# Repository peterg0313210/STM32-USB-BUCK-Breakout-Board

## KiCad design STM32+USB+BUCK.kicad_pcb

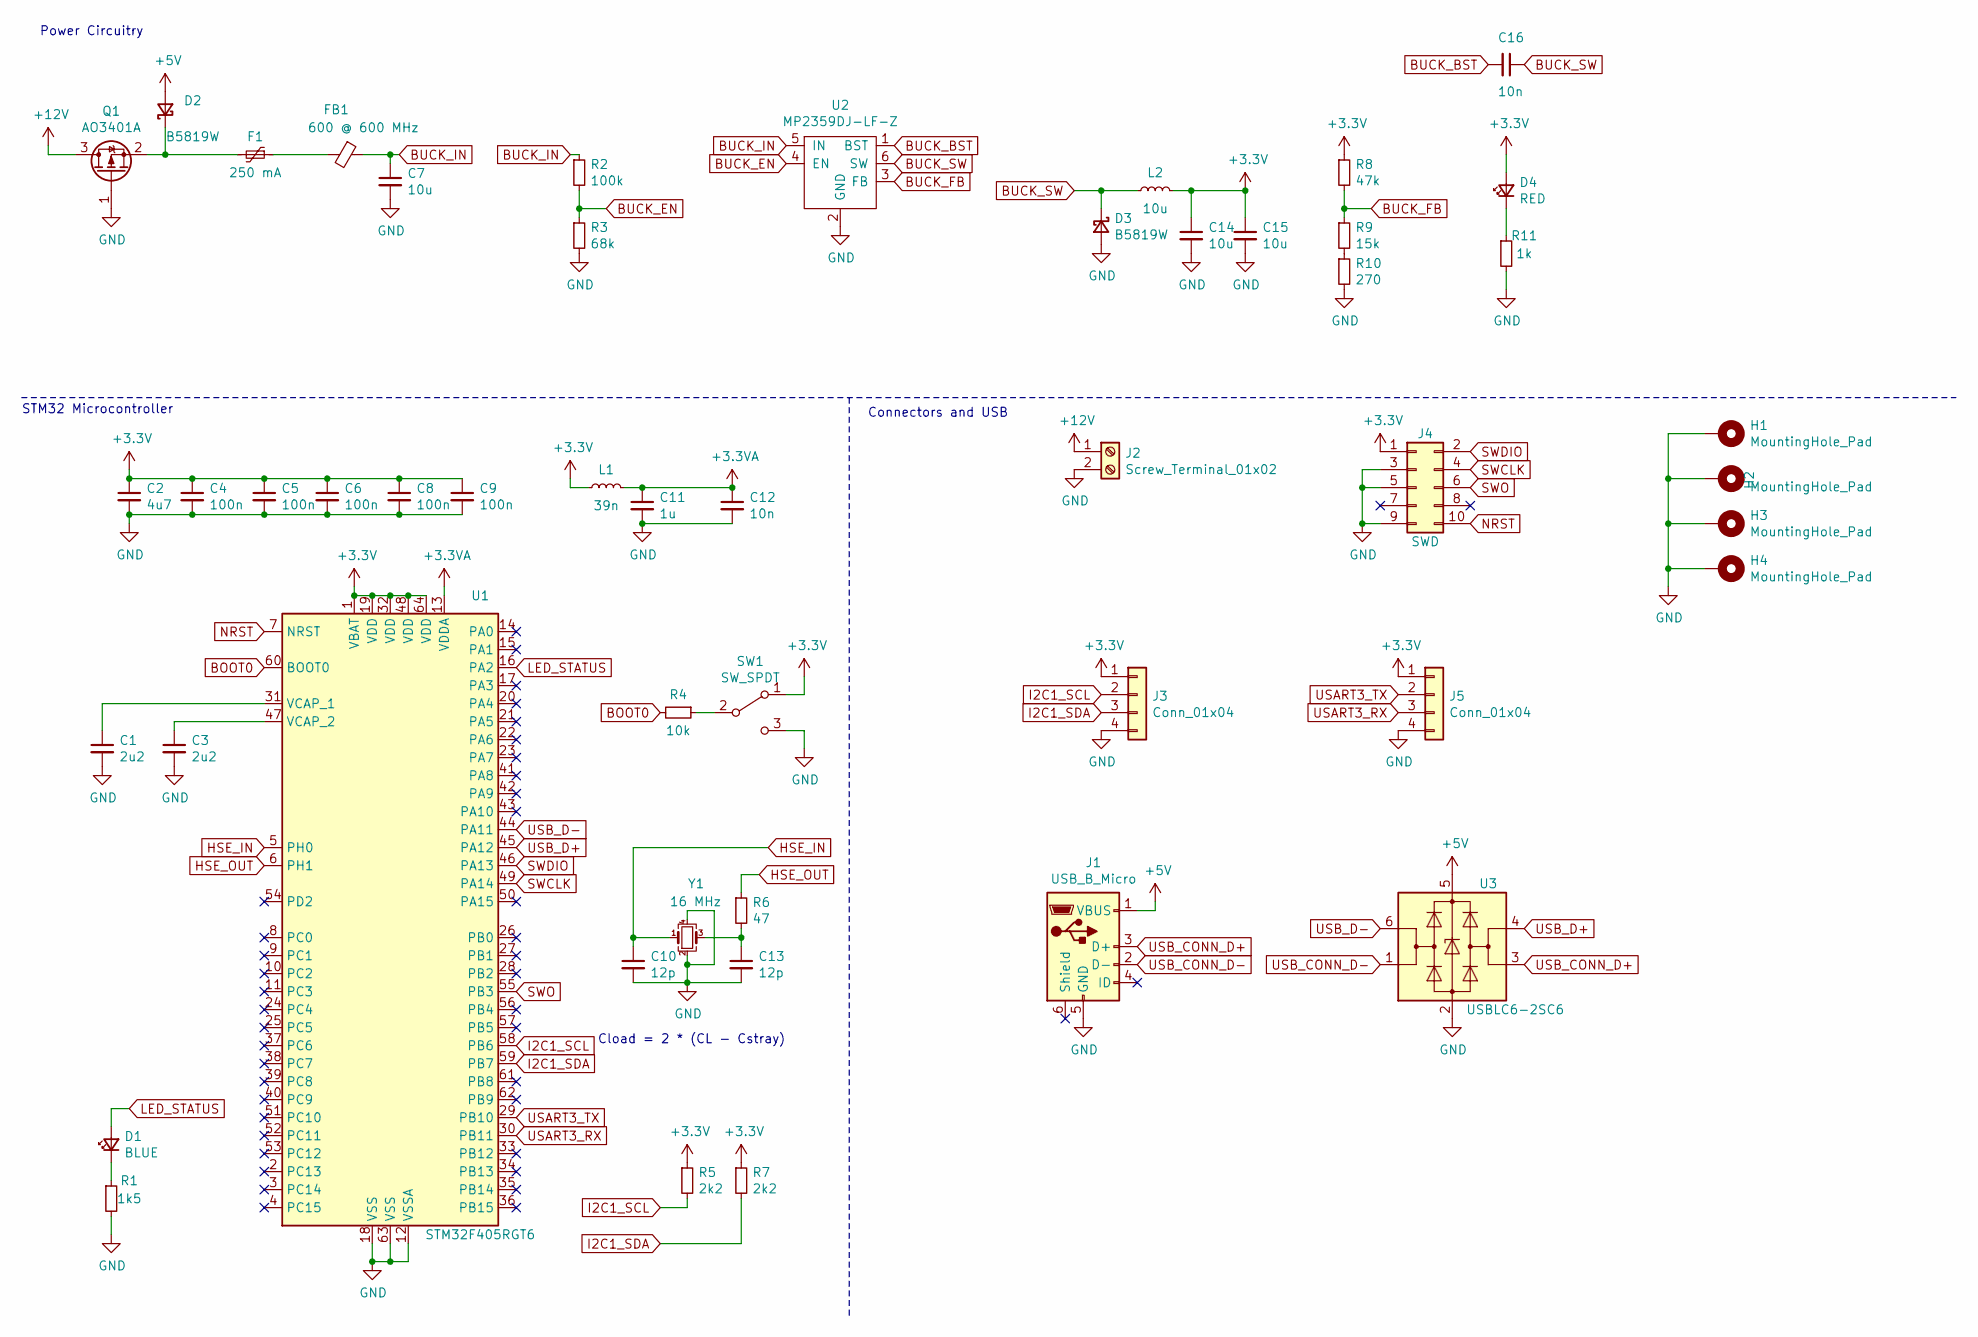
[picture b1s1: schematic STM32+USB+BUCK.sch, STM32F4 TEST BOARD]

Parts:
C1, C3: 2u2; C_0603_1608Metric
C2: 4u7; C_0603_1608Metric
C4, C5, C6, C8, C9: 100n; C_0402_1005Metric
C7, C14, C15: 10u; C_1206_3216Metric
C10, C13: 12p; C_0402_1005Metric
C11: 1u; C_0402_1005Metric
C12, C16: 10n; C_0603_1608Metric
D1: BLUE; LED_0603_1608Metric
D2, D3: B5819W; D_SOD-123
D4: RED; LED_0603_1608Metric
F1: 250 mA; Fuse_1206_3216Metric
FB1: 600 @ 600 MHz; L_0805_2012Metric
H1, H2, H3, H4: MountingHole_Pad; MountingHole_4.3mm_M4_Pad
J1: USB_B_Micro; USB_Micro-B_Molex-105017-0001
J2: Screw_Terminal_01x02; TerminalBlock_Phoenix_PT-1,5-2-3.5-H_1x02_P3.50mm_Horizontal
J3, J5: Conn_01x04; Molex_PicoBlade_53048-0410_1x04_P1.25mm_Horizontal
J4: SWD; PinHeader_2x05_P1.27mm_Vertical_SMD
L1: 39n; L_0402_1005Metric
L2: 10u; L_Sunlord_MWSA0518_5.4x5.2mm
Q1: AO3401A; SOT-23
R1: 1k5; R_0603_1608Metric
R2: 100k; R_0603_1608Metric
R3: 68k; R_0603_1608Metric
R4: 10k; R_0402_1005Metric
R5, R7: 2k2; R_0402_1005Metric
R6: 47; R_0402_1005Metric
R8: 47k; R_0603_1608Metric
R9: 15k; R_0603_1608Metric
R10: 270; R_0603_1608Metric
R11: 1k; R_0603_1608Metric
SW1: SW_SPDT; SW_SPDT_PCM12
U1: STM32F405RGT6; LQFP-64_10x10mm_P0.5mm
U2: MP2359DJ-LF-Z; SOT-23-6
U3: USBLC6-2SC6; SOT-23-6
Y1: 16 MHz; Crystal_SMD_3225-4Pin_3.2x2.5mm

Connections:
+3.3VA: C11.1, C12.1, L1.2, U1.13 (VDDA)
+3V3: C2.1, C4.1, C5.1, C6.1, C8.1, C9.1, C14.1, C15.1, D4.2 (A), J3.1, J4.1, J5.1, L1.1, L2.2, R5.1, R7.1, R8.1, SW1.1 (A), U1.1 (VBAT), U1.19 (VDD), U1.32 (VDD), U1.48 (VDD), U1.64 (VDD)
+5V: D2.2 (A), J1.1 (VBUS), U3.5 (VBUS)
+12V: J2.1, Q1.3 (D)
BOOT0: R4.2, U1.60 (BOOT0)
BUCK_BST: C16.2, U2.1 (BST)
BUCK_EN: R2.2, R3.1, U2.4 (EN)
BUCK_FB: R8.2, R9.1, U2.3 (FB)
BUCK_IN: C7.1, FB1.1, R2.1, U2.5 (IN)
BUCK_SW: C16.1, D3.1 (K), L2.1, U2.6 (SW)
GND: C1.2, C2.2, C3.2, C4.2, C5.2, C6.2, C7.2, C8.2, C9.2, C10.2, C11.2, C12.2, C13.2, C14.2, C15.2, D3.2 (A), H1.1, H2.1, H3.1, H4.1, J1.5 (GND), J2.2, J3.4, J4.3, J4.5, J4.9, J5.4, Q1.1 (G), R1.2, R3.2, R10.2, R11.2, SW1.3 (C), U1.12 (VSSA), U1.18 (VSS), U1.63 (VSS), U2.2 (GND), U3.2 (GND), Y1.2, Y1.4
HSE_IN: C10.1, U1.5 (PH0), Y1.1
HSE_OUT: R6.1, U1.6 (PH1)
I2C1_SCL: J3.2, R5.2, U1.58 (PB6)
I2C1_SDA: J3.3, R7.2, U1.59 (PB7)
LED_STATUS: D1.2 (A), U1.16 (PA2)
NRST: J4.10, U1.7 (NRST)
unnamed: C1.1, U1.31 (VCAP_1)
unnamed: C3.1, U1.47 (VCAP_2)
unnamed: C13.1, R6.2, Y1.3
unnamed: D1.1 (K), R1.1
unnamed: D2.1 (K), F1.2, Q1.2 (S)
unnamed: D4.1 (K), R11.1
unnamed: F1.1, FB1.2
unnamed: R4.1, SW1.2 (B)
unnamed: R9.2, R10.1
SWCLK: J4.4, U1.49 (PA14)
SWDIO: J4.2, U1.46 (PA13)
SWO: J4.6, U1.55 (PB3)
USART3_RX: J5.3, U1.30 (PB11)
USART3_TX: J5.2, U1.29 (PB10)
USB_CONN_D+: J1.3 (D+), U3.3 (I/O2)
USB_CONN_D-: J1.2 (D-), U3.1 (I/O1)
USB_D+: U1.45 (PA12), U3.4 (I/O2)
USB_D-: U1.44 (PA11), U3.6 (I/O1)

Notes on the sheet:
Cload = 2 * (CL - Cstray)
STM32 Microcontroller
Power Circuitry
Connectors and USB

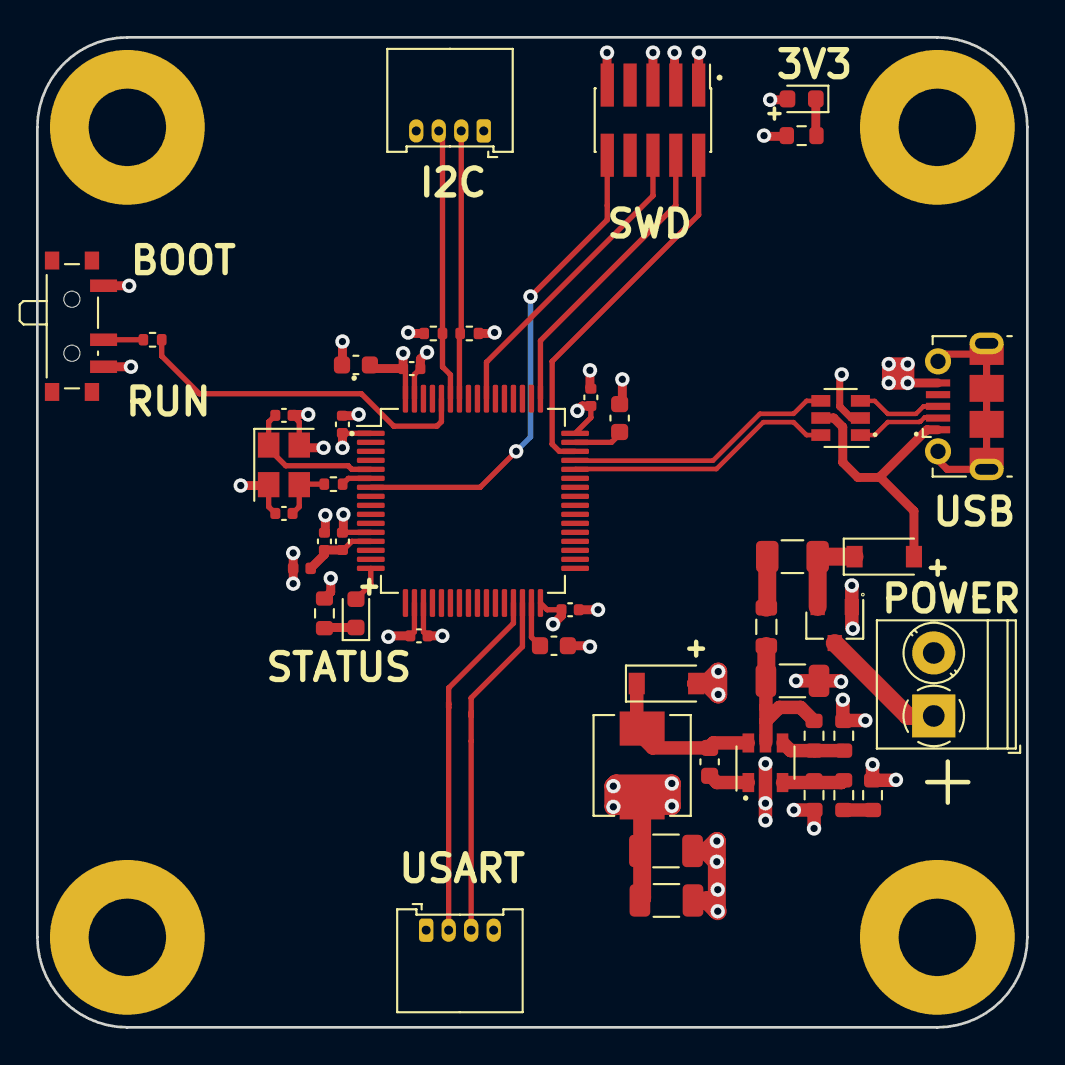
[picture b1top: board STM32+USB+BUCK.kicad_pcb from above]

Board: 4 copper layers, 55.0 x 55.0 mm, 50 parts (0 on the bottom side), 35 nets.

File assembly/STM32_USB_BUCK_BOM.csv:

Designator,Quantity,Value,Footprint,LSCS Part #
"C2,",1,4u7,0603,C19666
"C1, C3,",2,2u2,0603,C23630
"C4-C6, C8, C9,",5,100n,0402,C1525
"C10, C13,",2,12p,0402,C1547
"C11,",1,1u,0402,C52923
"C12, C16,",2,10n,0603, C57112
"C7, C14, C15,",3,10u,1206,C13585
"D1,",1,BLUE,0603, C72041
"D2, D3,",2,B5819W,SOD-123, C8598
"D4,",1,RED,0603, C2286
"F1,",1,250 mA,1206,C369159
"FB1,",1,600 @ 600 MHz,0805,C1017
"L1,",1,39n,0402, C26443
"L2,",1,10u,0503, C139506
"Q1,",1,AO3401A,SOT-23, C15127
"R1,",1,1k5,0603, C22843
"R2,",1,100k,0603, C25803
"R3,",1,68k,0603, C23231
"R4,",1,10k,0402, C25804
"R5, R7,",2,2k2,0402,C4190
"R6,",1,47,0402,C23182
"R8,",1,47k,0603,C25819
"R9,",1,15k,0603,C22809
"R10,",1,270,0603,C22966
"R11,",1,1k,0603,C21190
"U1,",1,STM32F405RGT6,Package_QFP:LQFP-64_10x10mm_P0.5mm,C15742
"U2,",1,MP2359DJ-LF-Z,SOT-23-6L,C14259
"U3,",1,USBLC6-2SC6,SOT-23-6L,C7519
"Y1,",1,16 MHz,SMD-3225_4P,C270482
